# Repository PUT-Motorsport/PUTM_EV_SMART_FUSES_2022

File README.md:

# PUTM_EV_SMART_FUSES_2022

## Description
The main principle behind the concept of Smart Fuses was adaptability and ease of resetting fuses, what the past designs couldn't achive. The board uses VN9D30Q100F High-side driver with integrated short-circuit detection and programmable interface based on reliable and fast SPI communication. It features 6 programmable channels, two of them are rated for 31,5A maximum flowing current the rest is rated for 14A. As mentioned used uCs can detect when one of the managed boards are

## Quick preview
The Smart Fuses board is responsible for two primary things:
- control over chips with integrated fuses based on mosfets,
- control over assi (auyonomus system status indicator) and buzzer.

## Basic flow chart
 <br/>
( basic concept of the program's flow, it may or may not change depending on the needs )

## Main Connector Pinout

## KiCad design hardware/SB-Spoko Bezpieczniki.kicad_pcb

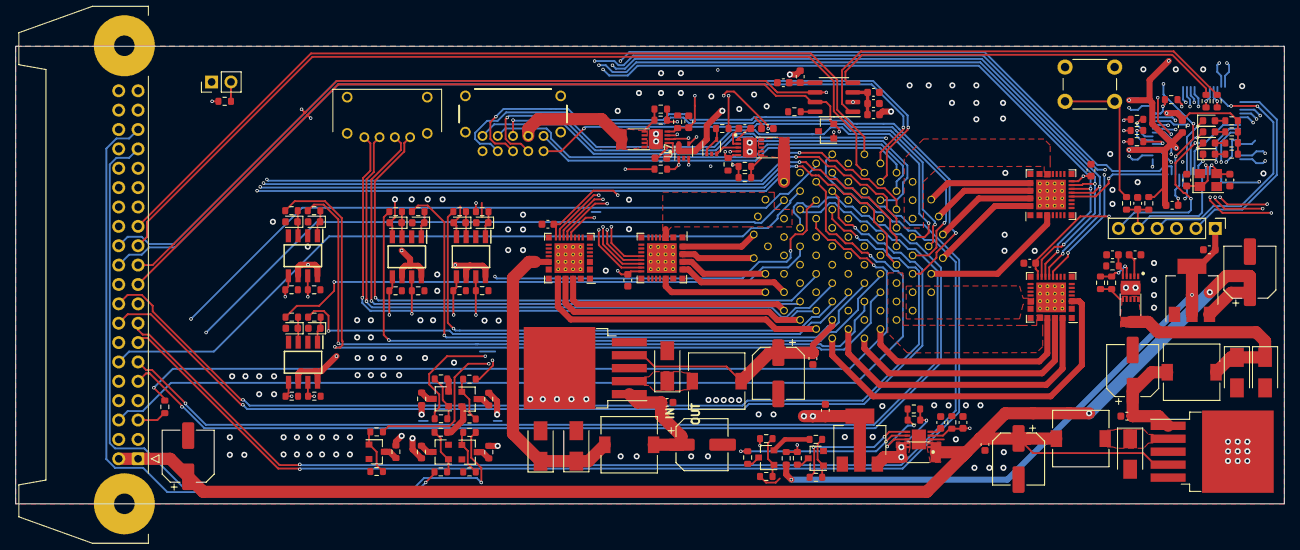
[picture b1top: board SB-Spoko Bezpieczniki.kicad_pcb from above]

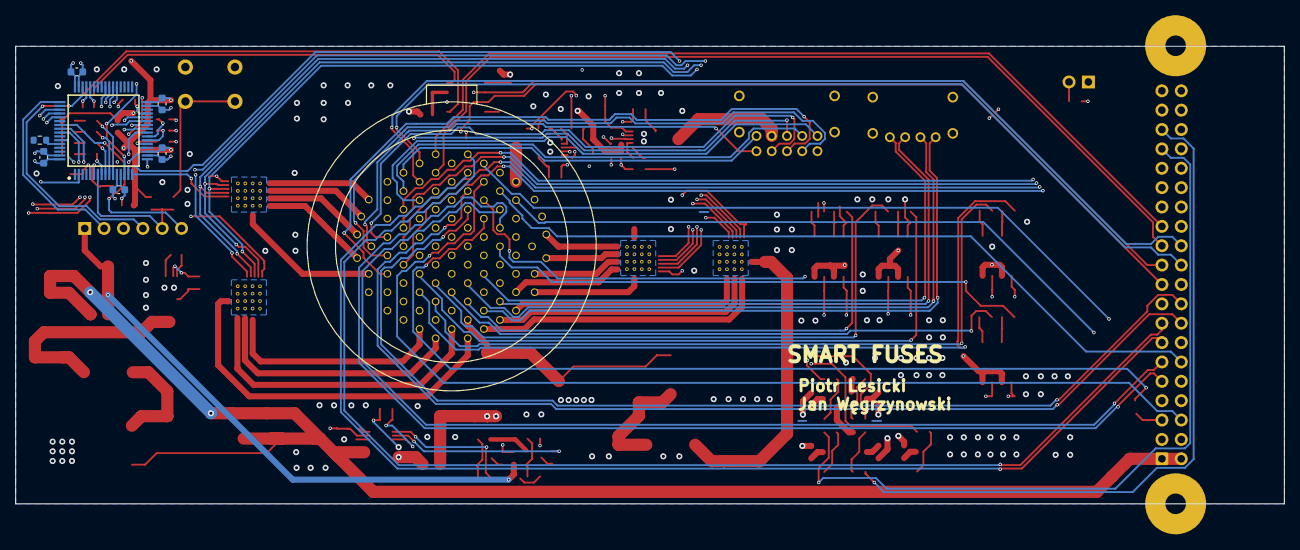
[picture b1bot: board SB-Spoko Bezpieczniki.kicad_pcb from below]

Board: 4 copper layers, 166.4 x 60.0 mm, 169 parts (8 on the bottom side), 179 nets.

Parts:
C1, C2, C3, C6, C7, C10, C11, C12, C13, C14, C21, C27, C29, C30, C31, C32, C33, C37, C39: 100nF; C_0603_1608Metric
C4, C5, C8, C9, C25, C36: 10pF; CP_Elec_6.3x7.7
C15, C17, C19: 10nF; C_0603_1608Metric
C16, C18, C20: 0; C_0603_1608Metric
C28: 10uF; C_0603_1608Metric
C34, C35: 22pF; C_0603_1608Metric
CLAMP1: 0; C_0603_1608Metric
D1, D2, D11, D12, D13, D14, D15, D16: D_SCH; D_0603_1608Metric
D3, D4: D_ZEN; D_SMA
D5, D6, D7, D8: D_SCH; D_SMA
D18: PESD2CAN.215; SOT-23
D19: I'M FINE; D_0603_1608Metric
D20: I_AM_ON_FIRE!!!; D_0603_1608Metric
D21: COULD_BE_BETTER; D_0603_1608Metric
D22: WHAT_THE_F?; D_0603_1608Metric
F1, F2, F3, F4: Polyfuse; Fuse_2010_5025Metric
FB1, FB2: 60R@100MHz; L_0603_1608Metric
FB3: FB; L_0603_1608Metric
IC1: STM32L4P5RET6; QFP50P1200X1200X160-64N
IC2, IC5, IC6: NIS4461MT1TXG; SON50P300X300X80-11N
IC4: NIS6351MT2TXG; SON50P300X300X80-11N-D
ILIM1, ILIM2, ILIM5, ILIM6, ILIM7, ILIM8: ?; R_0603_1608Metric
ILIM3, ILIM4: 0; R_0603_1608Metric
IMON1, IMON2, IMON3: 1k; R_0603_1608Metric
J1: SWD; PinHeader_1x06_P2.54mm_Vertical
J2: Conn_02x20_Odd_Even; IDC-Header_2x20-1MP_P2.54mm_Latch_Horizontal
J3: M80-8420445
J4: M80-8661022; M808661022
JP1: CAN_EXTARMINATOR; PinHeader_1x02_P2.54mm_Vertical
L1, L3: 22uH; L_7.3x7.3_H3.5
L2, L4: 22uH; L_7.3x7.3_H4.5
L5: L_Small; L_0603_1608Metric
O1, O2, O3, O5: FOD8802DR2_IMG; SOIC127P600X175-8N
Q1, Q2, Q3, Q4, Q5, Q7, Q8: Q_NMOS_GSD; SOT-23
R1, R2, R4, R17, R21, R25, R28, R31, R34, R42, R43, R50, R51, R61: 100; R_0603_1608Metric
R3, R7, R8, R11, R12, R15, R16, R18, R22, R26, R29, R32, R35, R48, R49, R53, R56: 10k; R_0603_1608Metric
R5, R6, R9, R10, R13, R14, R45, R46: --; R_0603_1608Metric
R19: 120; R_0603_1608Metric
R20, R44: 1k; R_0603_1608Metric
R23, R27, R30, R33, R36, R41, R47, R52, R55: 0; R_0603_1608Metric
R24: 100k; R_0603_1608Metric
R37, R38, R39, R40: 470; R_0603_1608Metric
R54: R_Small; R_0603_1608Metric
SW1: RESET; SW_PUSH_6mm
U1: AS222-35PN-933; AS222-35PN-933C-ver4-drill_0.72_size_1.02
U2: LM2596S-12; TO-263-5_TabPin3
U3: LM2596S-5; TO-263-5_TabPin3
U4, U6: LM317_SOT-223; SOT-223-3_TabPin2
U5, U7: MCP6001x-LT; SOT-353_SC-70-5
U11: MCP2558FD-xSN; SOIC-8_3.9x4.9mm_P1.27mm
U12, U13, U14, U15: SMART FUSE; QFN-32_EP_6x6_Pitch0.5mm
Y1: Crystal_GND24_Small; Crystal_SMD_3225-4Pin_3.2x2.5mm

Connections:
3.3V_STM_POWER: C11.1, C12.1, C13.1, C14.1, FB3.2, IC1.19 (VDD_1), IC1.32 (VDD_2), IC1.48 (VDDUSB), IC1.64 (VDD_3), L5.2, R3.1
3.3V_STM_REF+: C10.2, IC1.13 (VDDA/VREF+), L5.1
5V_CONVERT_24V: D4.1 (K), D6.1 (K), F3.1, IC5.6 (SRC_1), IC5.7 (SRC_2), IC5.8 (SRC_3), IC5.9 (SRC_4), IC5.10 (SRC_5), ILIM5.1, ILIM6.1, L4.1
+3V3: C1.2, C30.2, C31.2, C32.2, C37.1, FB2.1, FB3.1, J1.1, O1.6, O1.8, O2.6, O2.8, O3.6, O3.8, O5.6, O5.8, R37.2, R38.2, R39.2, R40.2, R56.2, U4.2 (VO), U5.5 (V+), U7.5 (V+), U12.16 (VDD), U13.16 (VDD), U14.16 (VDD), U15.16 (VDD)
+5V: C7.1, C9.1, C25.1, C36.1, F2.2, FB1.1, IC4.1 (VCC_1), IC4.2 (VCC_2), J2.1, J2.2, L2.2, U3.4 (FB), U4.3 (VI)
+24V: F1.2, F3.2, F4.2, IC2.11 (VCC), IC5.11 (VCC), IC6.11 (VCC), U1.51, U1.52, U1.59, U1.60, U1.61, U1.62, U1.70, U1.71, U1.72, U12.33 (VCC), U13.33 (VCC), U14.33 (VCC), U15.33 (VCC)
/Fusses/BSPD-ESB/EN/FAULT: IC6.3 (EN/FLT), U5.3 (+)
/Fusses/Fuse 3/VOUT_0: U15.3 (OUT_0A), U15.4 (OUT_0B)
/Fusses/Fuse 3/VOUT_1: U15.31 (OUT_1A), U15.32 (OUT_1B)
/Fusses/Supply/IMON: C15.1, IC5.5 (ISENSE), IMON2.1
/Fusses/TSAL/EN/FAULT: IC2.3 (EN/FLT), U7.3 (+)
/Fusses/WATER-POTENTIOMMETER/WATER/POT_EN: IC4.7 (EN), R41.1
/Fusses/WATER-POTENTIOMMETER/WATER/POT_FLAG: IC4.6 (FLAG), R42.1
/Inputs/CAN transreciver/+3V3_VIO: C29.1, FB2.2, U11.5 (VIO)
/Inputs/CAN transreciver/+5V_CAN_VDD: C27.1, C28.1, FB1.2, U11.3 (VDD)
/Inputs/CAN transreciver/SHDN: R47.1, U11.8 (S)
ASMS_24V: U1.55, U14.31 (OUT_1A), U14.32 (OUT_1B)
BAT_HV_24V: U1.15, U15.29 (OUT_2A), U15.30 (OUT_2B)
BOX_24V: U1.3, U12.31 (OUT_1A), U12.32 (OUT_1B)
BOX_DV_24V: U1.83, U1.84, U1.85, U14.25 (OUT_4A), U14.26 (OUT_4B)
BREAK_LIGHT_24V: U1.14, U12.25 (OUT_4A), U12.26 (OUT_4B)
BREAK_LIGHT_GATE: J2.33, R34.1
BREAK_LIGHT_IN: R36.1, U1.32
BSPD/EBS_24V: F4.1, IC6.6 (SRC_1), IC6.7 (SRC_2), IC6.8 (SRC_3), IC6.9 (SRC_4), IC6.10 (SRC_5), ILIM7.1, ILIM8.1, U1.8
BSPD/EBS_IMON: C19.1, IC1.25 (PC5), IC6.5 (ISENSE), IMON3.1
BSPD/EBS_STATE: IC1.24 (PC4), R61.1
BUZZER_CONTROL: R21.1, R52.1
BUZZER_IN: R23.1, U1.12
CAN_RX: R50.1, U11.4 (RXD)
CAN_TX: R51.1, U11.1 (TXD)
CAR_CAN+: D18.2 (A2), J2.19, JP1.1, U1.46, U11.7 (CANH)
CAR_CAN-: D18.1 (A1), J2.21, R19.2, U1.47, U11.6 (CANL)
DASH_24V: U1.98, U13.31 (OUT_1A), U13.32 (OUT_1B)
DIAGPORT_24V: U1.34, U15.25 (OUT_4A), U15.26 (OUT_4B)
DV_SENSE: R45.2, U1.64
DV_SENSE_SIG: IC1.53 (PC12), O5.7, R48.2
ETHERNET_RX+: J3.2, U1.23
ETHERNET_RX-: J3.1, U1.31
ETHERNET_TX+: J3.4, U1.33
ETHERNET_TX-: J3.3, U1.42
FAN_L_24V: U1.95, U13.27 (OUT_3A), U13.28 (OUT_3B)
FAN_MONO_24V: U1.7, U12.21 (OUT_5A), U12.22 (OUT_5B)
FAN_R_24V: U1.94, U13.25 (OUT_4A), U13.26 (OUT_4B)
FIREWALL_SENSE: R46.2, U1.74
FIREWALL_SENSE_SIG: IC1.52 (PC11), O5.5, R49.2
GND: C1.1, C2.2, C3.2, C4.2, C5.2, C6.2, C7.2, C8.2, C9.2, C10.1, C11.2, C12.2, C13.2, C14.2, C15.2, C16.2, C17.2, C18.2, C19.2, C20.2, C21.2, C25.2, C27.2, C28.2, C29.2, C30.1, C31.1, C32.1, C33.2, C34.1, C35.2, C36.2, C37.2, C39.2, CLAMP1.2, D1.2 (A), D2.2 (A), D3.2 (A), D4.2 (A), D5.2 (A), D6.2 (A), D7.2 (A), D8.2 (A), D11.2 (A), D12.2 (A), D13.2 (A), D14.2 (A), D15.2 (A), D16.2 (A), D18.3 (common), IC1.12 (VSSA/VREF-), IC1.18 (VSS_1), IC1.31 (VSS_2), IC1.47 (VSS_3), IC1.63 (VSS_4), IC2.1 (GND), IC4.3 (GND), IC5.1 (GND), IC6.1 (GND), IMON1.2, IMON2.2, IMON3.2, J1.3, J2.3, J2.4, J2.7, J2.14, J2.17, J2.20, J2.31, J2.34, J3.5 (MH1), J3.6 (MH2), J3.7 (MH3), J3.8 (MH4), J4.1, J4.MH1, J4.MH2, J4.MH3, J4.MH4, O1.2, O1.4, O2.2, O2.4, O3.2, O3.4, O5.2, O5.4, Q1.2 (S), Q2.2 (S), Q3.2 (S), Q4.2 (S), Q5.2 (S), Q7.2 (S), Q8.2 (S), R7.1, R8.1, R11.1, R12.1, R15.1, R16.1, R18.2, R22.2, R24.1, R26.2, R29.2, R32.2, R35.2, R44.2, R47.2, R48.1, R49.1, R53.2, SW1.1, U1.16, U1.21, U1.22, U1.29, U1.30, U1.39, U1.40, U1.41, U1.48, U1.49, U1.50, U1.54, U2.3 (GND), U2.5 (~ON/OFF), U3.3 (GND), U3.5 (~ON/OFF), U4.1 (ADJ), U5.2 (V-), U6.1 (ADJ), U7.2 (V-), U11.2 (VSS), U12.17 (GND), U13.17 (GND), U14.17 (GND), U15.17 (GND), Y1.2, Y1.4
HVD_SENSE: R9.2, U1.63
HVD_SENSE_SIG: IC1.40 (PC9), O2.7, R11.2
HV_SENSE: R10.2, U1.73
HV_SENSE_SIG: IC1.39 (PC8), O2.5, R12.2
INVERTER_24V: U1.1, U1.2, U1.10, U12.3 (OUT_0A), U12.4 (OUT_0B)
INVERTER_SENSE: R5.2, U1.53
INVERTER_SENSE_SIG: IC1.51 (PC10), O1.7, R7.2
INV_CAN+: J2.23, U1.57
INV_CAN-: J2.25, U1.56
JETSON_24V: U1.92, U1.93, U1.100, U14.21 (OUT_5A), U14.22 (OUT_5B)
LAPTIMER_24V: U1.96, U13.29 (OUT_2A), U13.30 (OUT_2B)
LED_1_CONTROL: IC1.57 (PB5), R28.1
LED_1_IN: R30.1, U1.4
LED_2_CONTROL: IC1.59 (PB7), R25.1
LED_2_IN: R27.1, U1.11
LIDAR_24V: U1.66, U14.29 (OUT_2A), U14.30 (OUT_2B)
MISO: R2.1, U12.15 (SDO), U13.15 (SDO), U14.15 (SDO), U15.15 (SDO)
MONO_NTC: J2.8, U1.25
MOSI: R4.1, U12.14 (SDI), U13.14 (SDI), U14.14 (SDI), U15.14 (SDI)
MOTEC_24V: U1.6, U12.27 (OUT_3A), U12.28 (OUT_3B)
N_RST: C33.1, IC1.7 (NRST), J1.5, R3.2, R20.2
unnamed: C2.1, C4.1, L3.2, U2.1 (VIN)
unnamed: C3.1, C5.1, L4.2, U3.1 (VIN)
unnamed: C16.1, IC5.2 (DV/DT)
unnamed: C18.1, IC2.2 (DV/DT)
unnamed: C20.1, IC6.2 (DV/DT)
unnamed: CLAMP1.1, IC4.5 (VC_SEL)
unnamed: D1.1 (K), O1.1, R5.1
unnamed: D2.1 (K), O1.3, R6.1
unnamed: D7.1 (K), L1.1, U2.2 (OUT)
unnamed: D8.1 (K), L2.1, U3.2 (OUT)
unnamed: D11.1 (K), O2.1, R9.1
unnamed: D12.1 (K), O2.3, R10.1
unnamed: D13.1 (K), O3.1, R13.1
unnamed: D14.1 (K), O3.3, R14.1
unnamed: D15.1 (K), O5.1, R45.1
unnamed: D16.1 (K), O5.3, R46.1
unnamed: D19.2 (A), R37.1
unnamed: D20.2 (A), R38.1
unnamed: D21.2 (A), R39.1
unnamed: D22.2 (A), R40.1
unnamed: IC1.21 (PA5), R1.2
unnamed: IC1.22 (PA6), R2.2
unnamed: IC1.23 (PA7), R4.2
unnamed: IC1.29 (PB10), R52.2
unnamed: IC1.44 (PA11), R50.2
unnamed: IC1.45 (PA12), R51.2
unnamed: IC1.60 (PH3-BOOT0), R24.2
unnamed: IC2.4 (ILIM), ILIM1.2, ILIM2.2
unnamed: IC4.8 (ILIM), ILIM3.1, ILIM4.1
unnamed: IC5.4 (ILIM), ILIM5.2, ILIM6.2
unnamed: IC6.4 (ILIM), ILIM7.2, ILIM8.2
unnamed: J2.5, R54.1
unnamed: JP1.2, R19.1
unnamed: Q1.1 (G), R21.2, R22.1
unnamed: Q1.3 (D), R23.2
unnamed: Q2.1 (G), R28.2, R29.1
unnamed: Q2.3 (D), R30.2
unnamed: Q3.1 (G), R34.2, R35.1
unnamed: Q3.3 (D), R36.2
unnamed: Q4.1 (G), R31.2, R32.1
unnamed: Q4.3 (D), R33.2
unnamed: Q5.1 (G), R25.2, R26.1
unnamed: Q5.3 (D), R27.2
unnamed: Q7.1 (G), R17.2, R18.1
unnamed: Q7.3 (D), R41.2
unnamed: Q8.1 (G), R42.2, R53.1
unnamed: Q8.3 (D), R55.2
unnamed: R20.1, SW1.2
unnamed: R43.2, U7.1, U7.4 (-)
unnamed: R61.2, U5.1, U5.4 (-)
ODRIVE_24V: U1.86, U1.87, U1.88, U13.21 (OUT_5A), U13.22 (OUT_5B)
POT_?V: C21.1, U1.65, U6.2 (VO)
PUMP_12V: C6.1, C8.1, L1.2, U1.44, U2.4 (FB)
PUMP_24V: D3.1 (K), D5.1 (K), L3.1, U15.21 (OUT_5A), U15.22 (OUT_5B)
RES_COS+: J2.13, U1.36
RES_COS-: J2.15, U1.35
RES_SIN+: J2.9, U1.19
RES_SIN-: J2.11, U1.18
RTDS_GATE: J2.35, R31.1
RTDS_IN: R33.1, U1.13
SCK: R1.1, U12.13 (SCK), U13.13 (SCK), U14.13 (SCK), U15.13 (SCK)
SPARE_1_24V: U1.45, U14.3 (OUT_0A), U14.4 (OUT_0B)
SPARE_1_SENSE: R6.2, U1.20
SPARE_1_SENSE_SIG: IC1.2 (PC13), O1.5, R8.2
SPARE_2_24V: U1.24, U15.27 (OUT_3A), U15.28 (OUT_3B)
SPARE_2_SENSE: R13.2, U1.27
SPARE_2_SENSE_SIG: IC1.37 (PC6), O3.7, R15.2
SPARE_3_SENSE: R14.2, U1.43
SPARE_3_SENSE_SIG: IC1.38 (PC7), O3.5, R16.2
SP_L+: J2.18, U1.38
SP_L-: J2.16, U1.37
SS_0: IC1.15 (PA1), U12.12 (CSN)
SS_1: IC1.16 (PA2), U13.12 (CSN)
SS_2: IC1.17 (PA3), U14.12 (CSN)
SS_3: IC1.20 (PA4), U15.12 (CSN)
STM_???: D22.1 (K), IC1.8 (PC0)
STM_CKL_OUT: C35.1, IC1.6 (PH1-OSC_OUT), Y1.1
STM_CLK_IN: C34.2, IC1.5 (PH0-OSC_IN), Y1.3
STM_FATAL_ERROR: D20.1 (K), IC1.9 (PC1)
STM_OK: D19.1 (K), IC1.11 (PC3)
STM_SOFT_ERROR: D21.1 (K), IC1.10 (PC2)
SWCLK: IC1.49 (PA14), J1.2
SWDIO: IC1.46 (PA13), J1.4
SWO: IC1.55 (PB3), J1.6
TSAL_24V: F1.1, IC2.6 (SRC_1), IC2.7 (SRC_2), IC2.8 (SRC_3), IC2.9 (SRC_4), IC2.10 (SRC_5), ILIM1.1, ILIM2.1, J4.9
TSAL_DASH_LED_GREEN: J4.3, U1.91
TSAL_DASH_LED_RED: J4.2, U1.90
TSAL_HV_AIR1: J4.6, U1.69
TSAL_HV_AIR2: J4.10, U1.77
TSAL_HV_BAT_SIG: J4.7, U1.78
TSAL_HV_INV_SIG: J4.8, U1.58
TSAL_IMON: C17.1, IC1.14 (PA0), IC2.5 (ISENSE), IMON1.1
TSAL_LED_GREEN: J4.5, U1.97
TSAL_LED_RED: J4.4, U1.89
TSAL_STATE: IC1.27 (PB1), R43.1
TSAL/ASSI_24V: U1.5, U12.29 (OUT_2A), U12.30 (OUT_2B)
USB_DEBUG_DM: J2.24, U1.68
USB_DEBUG_DP: J2.22, U1.67
WATER_1_PRESSURE: J2.6, U1.26
WATER_2_PRESSURE: R54.2, U1.28
WATER_5V: F2.1, IC4.9 (SRC_1), IC4.10 (SRC_2), ILIM3.2, ILIM4.2, U1.75, U6.3 (VI)
WATER_NTC_1: J2.12, U1.17
WATER_NTC_2: J2.10, U1.9
WATER/POT_ENABLE: IC1.28 (PB2), R17.1
WATER/POT_IMON: C39.1, IC1.26 (PB0), IC4.4 (IMON), R44.1
WATER/POT_STATE: IC1.56 (PB4), R55.1, R56.1
WHEEL_SPEED_1_24V: U1.99, U13.3 (OUT_0A), U13.4 (OUT_0B)
WHEEL_SPEED_2_24V: U1.76, U14.27 (OUT_3A), U14.28 (OUT_3B)
WSS_FL: J2.38, U1.80
WSS_FR: J2.40, U1.82
WSS_RL: J2.37, U1.79
WSS_RR: J2.39, U1.81

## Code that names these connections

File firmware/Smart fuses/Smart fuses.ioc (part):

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Mcu.Name=STM32L4P5R(G-E)Tx
Mcu.Package=LQFP64
Mcu.UserName=STM32L4P5RGTx
PA0.Signal=ADCx_IN5
PA1.GPIOParameters=GPIO_PuPd
PA1.GPIO_PuPd=GPIO_NOPULL
PA1.Signal=GPIO_Output
PA11.Mode=CAN_Activate
PA11.Signal=CAN1_RX
PA12.Mode=CAN_Activate
PA12.Signal=CAN1_TX
PA13\ (JTMS/SWDIO).Mode=Trace_Asynchronous_SW
PA13\ (JTMS/SWDIO).Signal=SYS_JTMS-SWDIO
PA14\ (JTCK/SWCLK).Mode=Trace_Asynchronous_SW
PA14\ (JTCK/SWCLK).Signal=SYS_JTCK-SWCLK
PA2.Signal=GPIO_Output
PA3.Signal=GPIO_Output
PA4.Signal=GPIO_Output
PA5.GPIOParameters=GPIO_PuPd
PA5.GPIO_PuPd=GPIO_PULLDOWN
PA5.Mode=Full_Duplex_Master
PA5.Signal=SPI1_SCK
PA6.GPIOParameters=GPIO_PuPd
PA6.GPIO_PuPd=GPIO_PULLDOWN
PA6.Mode=Full_Duplex_Master
PA6.Signal=SPI1_MISO
PA7.GPIOParameters=GPIO_PuPd
PA7.GPIO_PuPd=GPIO_PULLDOWN
PA7.Mode=Full_Duplex_Master
PA7.Signal=SPI1_MOSI
PB0.Signal=ADCx_IN15
PB1.Signal=ADCx_IN16
PB10.Signal=GPIO_Output
PB2.GPIOParameters=GPIO_PuPd
PB2.GPIO_PuPd=GPIO_PULLUP
PB2.Signal=GPIO_Output
PB3\ (JTDO/TRACESWO).Mode=Trace_Asynchronous_SW
PB3\ (JTDO/TRACESWO).Signal=SYS_JTDO-SWO
PB4\ (NJTRST).Signal=GPIO_Input
PB5.GPIOParameters=GPIO_PuPd
PB5.GPIO_PuPd=GPIO_NOPULL
PB5.Signal=GPIO_Output
PB7.Signal=GPIO_Output
PB9.Signal=GPIO_Output
PC0.Signal=GPIO_Output
PC1.Signal=GPIO_Output
PC10.Signal=GPIO_Input
PC11.Signal=GPIO_Input
PC12.Signal=GPIO_Input
PC13.Signal=GPIO_Input
PC2.Signal=GPIO_Output
PC3.Signal=GPIO_Output
PC4.Signal=ADCx_IN13
PC5.Signal=ADCx_IN14
PC6.Signal=GPIO_Input
PC7.Signal=GPIO_Input
PC8.Signal=GPIO_Input
PC9.Signal=GPIO_Input
PH0-OSC_IN\ (PH0).Mode=HSE-External-Oscillator
PH0-OSC_IN\ (PH0).Signal=RCC_OSC_IN
PH1-OSC_OUT\ (PH1).Mode=HSE-External-Oscillator
PH1-OSC_OUT\ (PH1).Signal=RCC_OSC_OUT
RCC.HSE_VALUE=8000000
RCC.SYSCLKFreq_VALUE=120000000
RCC.SYSCLKSource=RCC_SYSCLKSOURCE_PLLCLK
board=custom

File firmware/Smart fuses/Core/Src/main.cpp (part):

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GpioOutElement led_warning_1(GPIOC, GPIO_PIN_2, true);
GpioOutElement led_ok(GPIOC, GPIO_PIN_3, true);

GpioOutElement led_1_control(GPIOB, GPIO_PIN_5, false);
GpioOutElement led_2_control(GPIOB, GPIO_PIN_7, false);

Buzzer buzzer_control(GPIOB, GPIO_PIN_10, false, buzzer_signal_lenght);//(GPIOC, GPIO_PIN_0, false, buzzer_signal_lenght);

GpioOutElement water_pot_enable(GPIOB, GPIO_PIN_2, true);

GpioInElement water_pot_state(GPIOB, GPIO_PIN_4, false);

GpioInElement spare_2_sense_sig(GPIOC, GPIO_PIN_6, false);
GpioInElement spare_3_sense_sig(GPIOC, GPIO_PIN_7, false);
GpioInElement hv_sense_sig(GPIOC, GPIO_PIN_8, false);
GpioInElement hvd_sense_sig(GPIOC, GPIO_PIN_9, false);
GpioInElement inverter_sense_sig(GPIOC, GPIO_PIN_10, false);
GpioInElement firewall_sense_sig(GPIOC, GPIO_PIN_11, false);
GpioInElement dv_sense_sig(GPIOC, GPIO_PIN_12, false);
GpioInElement spare_1_sense_sig(GPIOC, GPIO_PIN_13, false);

CAN_FilterTypeDef can_filtering_config;

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
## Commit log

2021-12-14 Smart fusses first commit
2021-12-14 changed the name of the folder from SB... -> hardware
2021-12-14 removed power_2, becaouse unnecessary
2021-12-17 1. added 2X20 connector, \n 2. changed the footprints of schootkies and zenner diodes to a bigger ones, \n 3. changed pcb layout entirely couse duck me, that connector i too duking BIG.
2022-01-09 Updated to be compatible with KiCad 6.0.0, changed chematics layouts to fit in A4 worksheet and finished routing the rest of the signals.
2022-01-16 changed clock and 5v converter coils, footprints rearrange commponets to fit the need now the board connector is vertical not horizontal relative to the pcb's longest side
2022-01-22 minor improvements
2022-01-23 Plz Janek powiedz mi ze jest ok
2022-01-23 added traceswo from pin 55 to progrmator
2022-01-23 preproduction bug fixes
2022-01-23 smol changes
2022-01-23 other minor changes
2022-01-23 another minor changes
2022-03-15 firmware initial commit
2022-03-30 firmware update
2022-04-20 lets gooooooooooooooooooooooooooooooooooooo fuses workgit add *git add *git add *git add *git add *git add *
2022-04-20 fuses.h strucure development
2022-05-10 new gpio element lib for easier gpio management, updated fuses lib
2022-05-12 neet the lib for smart fuses works
2022-05-17 fuck
2022-05-26 some stuff
2022-05-27 jolo
2022-05-28 changed the order of pins, and started first changes for a v2 board
2022-05-28 currected autosport connector
2022-05-29 currected sf autosport connector, also updated firmware to better handle the showing of board status throught the on board LEDs
2022-05-29 minor changes
2022-05-29 resolving conflicts
2022-05-29 implemented a bit of can interface
2022-06-07 major schematic update, changed optocouplers for different, added new fuses for 5v supply for water and potentiometers and 24v supply for BSPD/ESB, updated autosport connector, and some other changes
2022-06-10 changed some footprints for clarity, and made some progress on board
2022-06-12 finished new wersion of the board
2022-06-13 debuged the board, changed one opto for mosfet, changed the way water and potentiometers were supplied. Also standrised opamps (yoinked opamps from data Data_Acquisition_Cards)
2022-06-16 currected TSAL, cause it can't be controled via external logic
2022-06-20 curected tsal supply, added sending of all smartfuses related frames, changed a nameing scheme for some classes/structs ex. for better clarity
2022-06-21 nameing scheme update
2022-06-21 woring on some stuff idk
2022-06-21 extended smart fuse lib, added a fan control
2022-06-22 changed function pointer to delegate provided by etl library
2022-06-22 debuged the program, now it's working
2022-06-28 saved current progress
2022-07-22 changed the software to work on a new board
2022-08-07 gitignore update
2022-08-07 firmware update - latest stable version, without software overcurrent protection
2022-08-07 configured overcurrent protection
2022-09-02 branch for the verion of protection without current over/underprotection
2022-09-03 changed sf settings so every one of them has a custom settings, also add a premade channel_off_setting for ease of specifing which channel should be turned off
2022-09-28 Added ASSI control, added GpioOutHandler responsible for overseeing the timing for blinking leds, added a type of GpioOutElement - Buzzer responsible for custom buzzer control
2022-09-29 LibCan update and soft using can's new features also updated
2022-10-05 deleted unnecessary files
2022-10-05 changes in untracked files
2023-07-10 increased max current and changed reading mode of sf to filtered

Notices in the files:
firmware/Smart fuses/Core/Src/main.cpp:
Copyright (c) 2022 STMicroelectronics.
All rights reserved.
This software is licensed under terms that can be found in the LICENSE file
